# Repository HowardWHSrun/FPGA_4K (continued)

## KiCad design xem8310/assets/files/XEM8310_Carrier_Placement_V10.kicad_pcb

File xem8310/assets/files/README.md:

# HDMI Extension Board V21 downloads

[Full portable KiCad ZIP](HDMI_Extension_Board_V21_Full_KiCad.zip) · [Project guide and checks](../../../hardware/hdmi-extension-board/dated/2026-11-02/v21/project/README.md) · [Schematic PDF](../schematic-v21.pdf)

Extract the entire ZIP to edit. Individual native files are also supplied for inspection. Original saved files are retained in the package records.

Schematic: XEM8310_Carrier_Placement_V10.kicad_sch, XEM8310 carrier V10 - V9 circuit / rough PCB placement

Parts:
C4: 100 nF / 10 V; C4; Manufacturer_PN C0402C104K8PACTU
C5: 220 µF / 25 V; C5; Manufacturer_PN EEE-FK1E221P
C6: 100 nF / 25 V; C6; Manufacturer_PN TMK105BJ104KV-F
C7: 0.1 u; C7; Manufacturer_PN C0402C104K8PACTU
C8: 0.1 u; C8; Manufacturer_PN C0402C104K8PACTU
C9: 0.1 u; C9; Manufacturer_PN C0402C104K8PACTU
C10: 0.1 u; C10; Manufacturer_PN C0402C104K8PACTU
C11: 0.1 u; C11; Manufacturer_PN C0402C104K8PACTU
C12: 0.1 u; C12; Manufacturer_PN C0402C104K8PACTU
C13: 0.1 u; C13; Manufacturer_PN C0402C104K8PACTU
C14: 0.1 u; C14; Manufacturer_PN C0402C104K8PACTU
C15: 0.1 u; C15; Manufacturer_PN C0402C104K8PACTU
C16: 0.1 u; C16; Manufacturer_PN C0402C104K8PACTU
C17: 0.1 u; C17; Manufacturer_PN C0402C104K8PACTU
C18: 0.1 u; C18; Manufacturer_PN C0402C104K8PACTU
C19: 0.1 u; C19; Manufacturer_PN C0402C104K8PACTU
C20: 0.1 u; C20; Manufacturer_PN C0402C104K8PACTU
C27: 0.1 u; C27; Manufacturer_PN C0402C104K8PACTU
C28: 0.1 u; C28; Manufacturer_PN C0402C104K8PACTU
C31: 0.1 u; C31; Manufacturer_PN C0402C104K8PACTU
C32: 0.1 u; C32; Manufacturer_PN C0402C104K8PACTU
C500: 4.7u; C500; Voltage 10V; MPN CL05A475MP5NRNC
C501: 100n; C501; Voltage 10V; MPN C0402C104K8PACTU
C502: 100n; C502; MPN C0402C104K8PACTU
C503: 18p; C503; MPN C0402C180J5GACTU
C504: 18p; C504; MPN C0402C180J5GACTU
C505: 100n; C505; MPN C0402C104K8PACTU
C506: 10n; C506; Voltage 16V; Tolerance 10%; MPN C0402C103K4RACTU
C507: 4.7u; C507; Voltage 6.3V; Tolerance 20%; MPN JMK105BBJ475MV-F
C508: 100n; C508; Voltage 10V; Tolerance 10%; MPN C0402C104K8PACTU
C509: 100n; C509; Voltage 10V; Tolerance 10%; MPN C0402C104K8PACTU
C510: 100n; C510; Voltage 10V; Tolerance 10%; MPN C0402C104K8PACTU
C511: 100n; C511; Voltage 10V; Tolerance 10%; MPN C0402C104K8PACTU
C512: 4.7u; C512; Voltage 6.3V; Tolerance 20%; MPN JMK105BBJ475MV-F
C513: 4.7u; C513; Voltage 6.3V; Tolerance 20%; MPN JMK105BBJ475MV-F
C514: 100n; C514; Voltage 10V; Tolerance 10%; MPN C0402C104K8PACTU
C515: 4.7u; C515; Voltage 6.3V; Tolerance 20%; MPN JMK105BBJ475MV-F
C516: 100n; C516; Voltage 10V; Tolerance 10%; MPN C0402C104K8PACTU
C517: 100n; C517; Voltage 10V; Tolerance 10%; MPN C0402C104K8PACTU
C518: 100n; C518; Voltage 10V; Tolerance 10%; MPN C0402C104K8PACTU
C519: 10n; C519; Voltage 16V; Tolerance 10%; MPN C0402C103K4RACTU
C520: 2.2uF 10V X7R; C520
C521: 2.2uF 10V X7R; C521
C600, C601: 2.2uF / 10V; C_0603_1608Metric; MPN GRM188R71A225KE15D
C610, C611, C612, C613, C620, C621, C622, C623, C710, C721, C722, C723, C724, C725, C726, C727, C728: 100nF / 16V; C_0603_1608Metric; MPN GRM188R71C104KA01D
C700: 100nF / 10V X7R; C700
C800, C801: 10uF / 25V X7R; C_1206_3216Metric; MPN GRM31CR71E106KA12L
C802, C803: 100nF / 25V X7R; C_0603_1608Metric; MPN GRM188R71E104KA01D
C810, C811, C812: 22uF / 16V X7R; C_1210_3225Metric; MPN GRM32ER71C226KEA8L
C1101, C1102, C1201, C1202, C1301, C1302, C1401, C1402, C1501, C1502, C1601, C1602, C1701, C1702, C1801, C1802: 100nF / 25V; C_AC_100nF_0603; Manufacturer_PN GRM188R71E104KA01D
C8100, C8101, C8200, C8201, C8300, C8301, C8400, C8401, C8500, C8501, C8600, C8601, C8700, C8701, C8800, C8801: 1uF / 25V X7R; C_0603_1608Metric; MPN GRM188R71E105KA12D
C8102, C8202, C8302, C8402, C8502, C8602, C8702, C8802: 47nF / 25V X7R; C_0603_1608Metric; MPN GRM188R71E473KA01D
D1: Green; D1; Manufacturer_PN 598-8070-107F
D2: Green; D2; Manufacturer_PN 598-8070-107F
D500: USBLC6-2SC6; D500
D810, D811, D812, D813, D814, D815, D816, D817: BAT54WS; D_SOD-323; MPN BAT54WS-7-F
FB500: 600R; FB500; MPN MI0603J601R-10
FB501: 600R; FB501; MPN MI0603J601R-10
FB502: 600R; FB502; MPN MI0603J601R-10
FB503: 220R @100MHz; FB503; MANUFACTURER_PN BLM21PG221SN1D
J3: 87831-1420; J3; Manufacturer_PN 87831-1420
J4: PJ-102AH; J4; Manufacturer_PN PJ-102AH
J5: 0455580003; J5; Manufacturer_PN 0455580003
J6: PCIe x4 electrical / x8 BRK edge; J6
J101, J102, J103, J104, J105, J106, J107, J108: 467651001 / GT + GPIO; MicroHDMI_467651001
J500: USB4110-GF-A; J500; MANUFACTURER_PN USB4110-GF-A
L800: 2.2uH / 20%; L_Coilcraft_XAL7070-XXX; MPN XAL7070-222MEC
MC1: BTE-040-01-F-D-A; MC1
MC2: BTE-040-01-F-D-A; MC2
MC3: QTH-040-01-F-D-DP-A; MC3
Q1: SI1922EDH-T1-GE3; Q1; Manufacturer_PN SI1922EDH-T1-GE3
R1: 0; R1; Manufacturer_PN CRCW06030000Z0EA; not fitted
R2: 0; R2; Manufacturer_PN CRCW06030000Z0EA
R3: 549 Ω / 1%; R3; Manufacturer_PN CRCW0402549RFKED
R4: 2.00 kΩ / 1%; R4; Manufacturer_PN CRCW04022K00FKED
R6: 0R / internal ADC ref; R6
R7: 0; R7; Manufacturer_PN CRCW06030000Z0EA
R8: 0; R8; Manufacturer_PN CRCW06030000Z0EA; not fitted
R9: 0; R9; Manufacturer_PN CRCW06030000Z0EA
R10: 0; R10; Manufacturer_PN CRCW06030000Z0EA
R11: 0; R11; Manufacturer_PN CRCW06030000Z0EA
R12: NoLoad; R12; not fitted
R13: 200 k; R13; Manufacturer_PN CRCW0402200KFKED
R14: 4.75 k; R14; Manufacturer_PN CRCW04024K75FKED
R15: 4.75 k; R15; Manufacturer_PN CRCW04024K75FKED
R16: NoLoad; R16; not fitted
R17: NoLoad; R17; not fitted
R18: 100 k; R18; Manufacturer_PN CRCW0402100KFKED
R20: NoLoad; R20; not fitted
R21: NoLoad; R21; not fitted
R22: NoLoad; R22; not fitted
R23: 200 k; R23; Manufacturer_PN CRCW0402200KFKED
R24: 100 k; R24; Manufacturer_PN CRCW0402100KFKED
R25: 100 k; R25; Manufacturer_PN CRCW0402100KFKED
R26: NoLoad; R26; not fitted
R27: 0; R27; Manufacturer_PN CRCW04020000Z0ED; not fitted
R28: 0; R28; Manufacturer_PN CRCW04020000Z0ED; not fitted
R29: 0; R29; Manufacturer_PN CRCW04020000Z0ED
R30: 4.75 k; R30; Manufacturer_PN CRCW04024K75FKED
R31: 4.75 k; R31; Manufacturer_PN CRCW04024K75FKED
R32: 100 k; R32; Manufacturer_PN CRCW0402100KFKED
R33: 100 k; R33; Manufacturer_PN CRCW0402100KFKED
R500: 5.1k 1%; R500; MPN CRCW04025K10FKEDC
R501: 5.1k 1%; R501; MPN CRCW04025K10FKEDC
R502: 100k; R502; Tolerance 1%; MPN CRCW0402100KFKED
R503: 100k; R503; Tolerance 1%; MPN CRCW0402100KFKED
R504: 2k; R504; Tolerance 1%; MPN CRCW04022K00FKED
R505: 10k; R505; Tolerance 1%; MPN CRCW040210K0FKED
R506: 10k; R506; Tolerance 1%; MPN CRCW040210K0FKED
R507: 12k 1%; R507; Tolerance 1%; MPN CRCW040212K0FKED
R508: 10k; R508
R509: 10k; R509
R600, R610, R611, R620, R621, R631, R641, R651, R661, R671, R681, R691, R720, R721, R722, R723, R724, R725, R726, R727, R8104, R8204, R8304, R8404, R8504, R8604, R8704, R8804: 10k / 1%; R_0603_1608Metric; MPN RC0603FR-0710KL
R612: 1M / 1%; R_0603_1608Metric; MPN RC0603FR-071ML
R613, R623, R804: 100k / 1%; R_0603_1608Metric; MPN RC0603FR-07100KL
R614, R615, R616, R624, R625, R626: 33R / 1%; R_0603_1608Metric; MPN RC0603FR-0733RL
R622: 68k / 1%; R_0603_1608Metric; MPN RC0603FR-0768KL
R700: 10k; R700
R701: 100k; R701
R730, R731, R732, R733, R734, R735, R736, R737: 1k / 1%; R_0603_1608Metric; MPN RC0603FR-071KL
R738: 140k / 0.1%; R_0603_1608Metric; MPN RT0603BRD07140KL
R739: 49.9k / 0.1%; R_0603_1608Metric; MPN RT0603BRD0749K9L
R800: 169k / 1%; R_0603_1608Metric; MPN RC0603FR-07169KL
R801: 36.1k / 1%; R_0603_1608Metric; MPN RT0603FRE0736K1L
R802: 45.3k / 0.1%; R_0603_1608Metric; MPN RT0603BRD0745K3L
R803, R8101, R8103, R8201, R8203, R8301, R8303, R8401, R8403, R8501, R8503, R8601, R8603, R8701, R8703, R8801, R8803: 10.0k / 0.1%; R_0603_1608Metric; MPN RT0603BRD0710KL
R8100, R8200, R8300, R8400, R8500, R8600, R8700, R8800: 15.0k / 0.1%; R_0603_1608Metric; MPN RT0603BRD0715KL
R8102, R8202, R8302, R8402, R8502, R8602, R8702, R8802: 19.1k / 0.1%; R_0603_1608Metric; MPN RT0603BRD0719K1L
R8105, R8205, R8305, R8405, R8505, R8605, R8705, R8805: 100R / 1%; R_0603_1608Metric; MPN RC0603FR-07100RL
R8106, R8206, R8306, R8406, R8506, R8606, R8706, R8806: 5.00k / 0.1%; R_0805_2012Metric; MPN PNM0805E5001BST5
SW600: Grayhill56P30_1P12T_N; Grayhill_56P30_1P12T_N; MPN 56P30-01-1-12N-F
SW700: JS202011JCQN; SW700
SW810, SW811, SW812, SW813, SW814, SW815, SW816, SW817: PRESS: OFF / RESET; SW_SPST_TL3342; MPN TL3342F160QG
TP9: SMDAT_VIO; TP9
TP10: SMDAT_PCIE; TP10
TP11: SMCLK_PCIE; TP11
TP12: SMCLK_VIO; TP12
TP13: PERST_VIO; TP13
TP14: PERST_PCIE; TP14
TP15: WAKE_VIO; TP15
TP16: WAKE_PCIE; TP16
TP20: +12V_PCIE_C; TP20
TP21: FAULT; TP21
TP800: BUCK_PG; TestPoint_Pad_D1.0mm
TP801: HDMI_3V3_RAW; TestPoint_Pad_D1.0mm
TP810, TP811, TP812, TP813, TP814, TP815, TP816, TP817: PORT_FAULT_N; TestPoint_Pad_D1.0mm
U2: PCA9306DCUR; U2; Manufacturer_PN PCA9306DCUR
U4: SN74AXC1T45DCK; U4; Manufacturer_PN SN74AXC1T45DCK
U5: AP22653AW6-7; U5; Manufacturer_PN AP22653AW6-7
U6: PCA9306DCUR; U6; Manufacturer_PN PCA9306DCUR
U501: FT232HQ; U501; MANUFACTURER_PN FT232HQ
U505: 93LC56B-E/MS; U505; MANUFACTURER_PN 93LC56B-E/MS
U506: TLV75533PDBVR; U506
U600: TLV75518PDBVR; SOT-23-5; MPN TLV75518PDBVR
U610, U611: TXU0304PWR; TSSOP-14_4.4x5mm_P0.65mm; MPN TXU0304PWR
U620: TPS3808G18DBVR; SOT-23-6; MPN TPS3808G18DBVR
U621: TPS3808G01DBVR; SOT-23-6; MPN TPS3808G01DBVR
U630, U631: SN74LVC1G17DBVR; SOT-23-5; MPN SN74LVC1G17DBVR
U700: TMUX1574PWR; U700
U710: SN74LVC540APWR; TSSOP-20_4.4x6.5mm_P0.65mm; MPN SN74LVC540APWR
U721, U722, U723, U724, U725, U726, U727, U728: TS3A27518EPWR; TSSOP-24_4.4x7.8mm_P0.65mm; MPN TS3A27518EPWR
U800: TPS56637RPAR; TI_RPA0010A_HotRod_3x3mm; MPN TPS56637RPAR
U810, U811, U812, U813, U814, U815, U816, U817: TPS259470LRPWR; TI_RPW0010A_HotRod_2x2mm; MPN TPS259470LRPWR
Y500: 12MHz; Y500; MPN ABM8-12.000MHZ-B2-T

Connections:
+1.2V_DDR: MC3.80 (+1.2V_DDR), R2.2
+1.8V: C4.1, C700.1, J3.2 (VREF), MC1.2 (+1.8V), R612.1, SW700.7 (EXTERNAL), U620.5 (SENSE_1V67), U700.16 (VDD)
+3.3V: MC2.70 (+3.3V), R3.2, R30.2, R31.2
+3.3VAUX_PCIE: C31.2, R13.2, R16.2, R17.2, R23.2, R26.2, U5.6 (OUT)
+3.3VAUX_PCIE_C: C32.2, J6.B10 (3.3Vaux), R18.2, U5.1 (IN)
+3.3V_PCIE_C: C12.2, J6.A9 (+3.3V), J6.A10 (+3.3V), J6.B8 (+3.3V), R21.2, U4.6 (Vccb)
+12V_PCIE_C: J6.A2 (+12V), J6.A3 (+12V), J6.B1 (+12V), J6.B2 (+12V), J6.B3 (+12V), TP20.1 (PIN_1)
+VDCIN: C5.1 (+), C6.2, C800.1, C801.1, C802.1, J4.1 (+VDCIN), J5.1, J5.2, J5.3, MC2.1 (+VDCIN), MC2.2 (+VDCIN), MC2.3 (+VDCIN), MC2.4 (+VDCIN), R4.2, R800.1, U800.8 (VIN)
/B64_L1N: J101.14 (GPIO_STIM_N), MC1.12 (B64_L1N)
/B64_L1P: J101.12 (GPIO_STIM_P), MC1.10 (B64_L1P)
/B64_L2N: J102.14 (GPIO_STIM_N), MC1.16 (B64_L2N)
/B64_L2P: J102.12 (GPIO_STIM_P), MC1.14 (B64_L2P)
/B64_L3N: J103.14 (GPIO_STIM_N), MC1.15 (B64_L3N)
/B64_L3P: J103.12 (GPIO_STIM_P), MC1.13 (B64_L3P)
/B64_L4N: J104.14 (GPIO_STIM_N), MC1.8 (B64_L4N)
/B64_L4P: J104.12 (GPIO_STIM_P), MC1.6 (B64_L4P)
/B64_L5N: J105.14 (GPIO_STIM_N), MC1.7 (B64_L5N)
/B64_L5P: J105.12 (GPIO_STIM_P), MC1.5 (B64_L5P)
/B64_L6N: J106.14 (GPIO_STIM_N), MC1.11 (B64_L6N)
/B64_L6P: J106.12 (GPIO_STIM_P), MC1.9 (B64_L6P)
/B64_L7N: J107.14 (GPIO_STIM_N), MC1.23 (B64_L7N)
/B64_L7P: J107.12 (GPIO_STIM_P), MC1.21 (B64_L7P)
/B64_L8N: J108.14 (GPIO_STIM_N), MC1.20 (B64_L8N)
/B64_L8P: J108.12 (GPIO_STIM_P), MC1.18 (B64_L8P)
/FTDI1V8_ANALOG: C518.2, U501.37 (VCCA)
/FTDI1V8_CORE: C517.2, U501.38 (VCORE)
/FTDI3V3_PHY: C515.1, C516.1, FB501.2, U501.3 (VPHY)
/FTDI3V3_PLL: C513.1, C514.1, FB500.2, U501.8 (VPLL)
/FTDI5V_FILTERED: C500.1, C501.1, FB502.2, U501.40 (VREGIN)
/FTDI_EECLK: R503.2, U501.44 (EECLK), U505.2 (CLK)
/FTDI_EECS: R502.1, U501.45 (EECS), U505.1 (CS)
/FTDI_EEDATA: R504.1, U501.43 (EEDATA), U505.3 (DI)
/HDMI_3V3_PG: D810.1 (K), D811.1 (K), D812.1 (K), D813.1 (K), D814.1 (K), D815.1 (K), D816.1 (K), D817.1 (K), R804.1, TP800.1 (1_1), U800.4 (PG)
/HDMI_3V3_RAW: C810.1, C811.1, C812.1, C8100.1, C8200.1, C8300.1, C8400.1, C8500.1, C8600.1, C8700.1, C8800.1, L800.2, R802.1, R804.2, R8100.1, R8102.1, R8104.1, R8200.1, R8202.1, R8204.1, R8300.1, R8302.1, R8304.1, R8400.1, R8402.1, R8404.1, R8500.1, R8502.1, R8504.1, R8600.1, R8602.1, R8604.1, R8700.1, R8702.1, R8704.1, R8800.1, R8802.1, R8804.1, TP801.1 (1_1), U810.5 (IN), U811.5 (IN), U812.5 (IN), U813.5 (IN), U814.5 (IN), U815.5 (IN), U816.5 (IN), U817.5 (IN)
/MGT_RXN0_224: C1102.2, MC3.3 (MGT_RXN0_224)
/MGT_RXN0_226: C1502.2, MC3.43 (MGT_RXN0_226)
/MGT_RXN1_224: C1202.2, MC3.7 (MGT_RXN1_224)
/MGT_RXN1_226: C1602.2, MC3.47 (MGT_RXN1_226)
/MGT_RXN2_224: C1302.2, MC3.11 (MGT_RXN2_224)
/MGT_RXN2_226: C1702.2, MC3.51 (MGT_RXN2_226)
/MGT_RXN3_224: C1402.2, MC3.15 (MGT_RXN3_224)
/MGT_RXN3_226: C1802.2, MC3.55 (MGT_RXN3_226)
/MGT_RXP0_224: C1101.2, MC3.1 (MGT_RXP0_224)
/MGT_RXP0_226: C1501.2, MC3.41 (MGT_RXP0_226)
/MGT_RXP1_224: C1201.2, MC3.5 (MGT_RXP1_224)
/MGT_RXP1_226: C1601.2, MC3.45 (MGT_RXP1_226)
/MGT_RXP2_224: C1301.2, MC3.9 (MGT_RXP2_224)
/MGT_RXP2_226: C1701.2, MC3.49 (MGT_RXP2_226)
/MGT_RXP3_224: C1401.2, MC3.13 (MGT_RXP3_224)
/MGT_RXP3_226: C1801.2, MC3.53 (MGT_RXP3_226)
/P1_3V3_PROTECTED: C8101.1, J101.19 (3V3_PROTECTED), U810.6 (OUT)
/P1_POWER_FAULT_N: R8104.2, TP810.1 (1_1), U810.4 (nFLT)
/P2_3V3_PROTECTED: C8201.1, J102.19 (3V3_PROTECTED), U811.6 (OUT)
/P2_POWER_FAULT_N: R8204.2, TP811.1 (1_1), U811.4 (nFLT)
/P3_3V3_PROTECTED: C8301.1, J103.19 (3V3_PROTECTED), U812.6 (OUT)
/P3_POWER_FAULT_N: R8304.2, TP812.1 (1_1), U812.4 (nFLT)
/P4_3V3_PROTECTED: C8401.1, J104.19 (3V3_PROTECTED), U813.6 (OUT)
/P4_POWER_FAULT_N: R8404.2, TP813.1 (1_1), U813.4 (nFLT)
/P5_3V3_PROTECTED: C8501.1, J105.19 (3V3_PROTECTED), U814.6 (OUT)
/P5_POWER_FAULT_N: R8504.2, TP814.1 (1_1), U814.4 (nFLT)
/P6_3V3_PROTECTED: C8601.1, J106.19 (3V3_PROTECTED), U815.6 (OUT)
/P6_POWER_FAULT_N: R8604.2, TP815.1 (1_1), U815.4 (nFLT)
/P7_3V3_PROTECTED: C8701.1, J107.19 (3V3_PROTECTED), U816.6 (OUT)
/P7_POWER_FAULT_N: R8704.2, TP816.1 (1_1), U816.4 (nFLT)
/P8_3V3_PROTECTED: C8801.1, J108.19 (3V3_PROTECTED), U817.6 (OUT)
/P8_POWER_FAULT_N: R8804.2, TP817.1 (1_1), U817.4 (nFLT)
/XEM_JTAG_MASTER_SEL: R701.1, SW700.6 (MUX_SEL_COMMON), U700.1 (SEL)
B64_L17N: MC1.44 (B64_L17N), R11.2
B64_L17P: MC1.42 (B64_L17P), R10.2
B64_L20N: MC1.40 (B64_L20N), R9.2
B64_L20P: MC1.38 (B64_L20P), R8.2
B67_T3U_N12: MC3.78 (B67_T3U_N12), R7.2
DGND: C4.2, C5.2 (-), C6.1, C9.1, C10.1, C11.1, C12.1, C27.1, C28.1, C31.1, C32.1, C520.2, C521.2, C600.2, C601.2, C610.2, C611.2, C612.2, C613.2, C620.2, C621.2, C622.2, C623.2, C700.2, C710.2, C721.2, C722.2, C723.2, C724.2, C725.2, C726.2, C727.2, C728.2, C800.2, C801.2, C802.2, C810.2, C811.2, C812.2, C8100.2, C8101.2, C8102.2, C8200.2, C8201.2, C8202.2, C8300.2, C8301.2, C8302.2, C8400.2, C8401.2, C8402.2, C8500.2, C8501.2, C8502.2, C8600.2, C8601.2, C8602.2, C8700.2, C8701.2, C8702.2, C8800.2, C8801.2, C8802.2, D1.1 (K), D2.1 (K), D500.2 (GND), J3.1 (DGND), J3.3 (DGND), J3.5 (DGND), J3.7 (DGND), J3.9 (DGND), J3.11 (DGND), J3.13 (DGND), J4.2 (DGND), J5.4, J5.5, J5.6, J6.A4 (GND), J6.A12 (GND), J6.A15 (GND), J6.A18 (GND), J6.A20 (GND), J6.A23 (GND), J6.A24 (GND), J6.A27 (GND), J6.A28 (GND), J6.A31 (GND), J6.A34 (GND), J6.A37 (GND), J6.A38 (GND), J6.A41 (GND), J6.A42 (GND), J6.A45 (GND), J6.A46 (GND), J6.A49 (GND), J6.B4 (GND), J6.B7 (GND), J6.B13 (GND), J6.B16 (GND), J6.B18 (GND), J6.B21 (GND), J6.B22 (GND), J6.B25 (GND), J6.B26 (GND), J6.B29 (GND), J6.B32 (GND), J6.B35 (GND), J6.B36 (GND), J6.B39 (GND), J6.B40 (GND), J6.B43 (GND), J6.B44 (GND), J6.B47 (GND), J6.B49 (GND), J101.4 (GND), J101.7 (GND), J101.10 (GND), J101.13 (GND), J101.16 (GND), J101.SH (SHELL), J102.4 (GND), J102.7 (GND), J102.10 (GND), J102.13 (GND), J102.16 (GND), J102.SH (SHELL), J103.4 (GND), J103.7 (GND), J103.10 (GND), J103.13 (GND), J103.16 (GND), J103.SH (SHELL), J104.4 (GND), J104.7 (GND), J104.10 (GND), J104.13 (GND), J104.16 (GND), J104.SH (SHELL), J105.4 (GND), J105.7 (GND), J105.10 (GND), J105.13 (GND), J105.16 (GND), J105.SH (SHELL), J106.4 (GND), J106.7 (GND), J106.10 (GND), J106.13 (GND), J106.16 (GND), J106.SH (SHELL), J107.4 (GND), J107.7 (GND), J107.10 (GND), J107.13 (GND), J107.16 (GND), J107.SH (SHELL), J108.4 (GND), J108.7 (GND), J108.10 (GND), J108.13 (GND), J108.16 (GND), J108.SH (SHELL), MC1.3 (DGND), MC1.29 (DGND), MC1.30 (DGND), MC1.59 (DGND), MC1.60 (DGND), MC1.77 (DGND), MC1.78 (DGND), MC2.5 (DGND), MC2.6 (DGND), MC2.7 (DGND), MC2.8 (DGND), MC2.33 (DGND), MC2.34 (DGND), MC2.67 (DGND), MC2.68 (DGND), MC2.73 (DGND), MC3.0 (CENTER_GROUND), Q1.1 (S1), Q1.4 (S2), R12.1, R22.1, R24.1, R32.1, R33.1, R600.2, R611.2, R612.2, R613.2, R621.1, R622.2, R623.2, R631.1, R641.1, R651.1, R661.1, R671.1, R681.1, R691.1, R700.2, R701.2, R730.2, R731.2, R732.2, R733.2, R734.2, R735.2, R736.2, R737.2, R739.1, R801.2, R803.2, R8101.2, R8103.2, R8106.2, R8201.2, R8203.2, R8206.2, R8301.2, R8303.2, R8306.2, R8401.2, R8403.2, R8406.2, R8501.2, R8503.2, R8506.2, R8601.2, R8603.2, R8606.2, R8701.2, R8703.2, R8706.2, R8801.2, R8803.2, R8806.2, SW700.3 (EXTERNAL), SW700.5 (ONBOARD), SW810.2, SW811.2, SW812.2, SW813.2, SW814.2, SW815.2, SW816.2, SW817.2, U2.1 (GND), U4.2 (GND), U4.5 (DIR), U5.2 (GND), U6.1 (GND), U506.2 (GND), U600.2 (GND), U610.7 (GND), U611.7 (GND), U620.2 (GND), U621.2 (GND), U630.3 (GND), U631.3 (GND), U700.8 (GND), U700.15 (~EN), U710.1 (~OE1), U710.10 (GND), U710.19 (~OE2), U721.5 (GND), U722.5 (GND), U723.5 (GND), U724.5 (GND), U725.5 (GND), U726.5 (GND), U727.5 (GND), U728.5 (GND), U800.3 (AGND), U800.9 (PGND), U800.10 (MODE), U810.8 (GND), U811.8 (GND), U812.8 (GND), U813.8 (GND), U814.8 (GND), U815.8 (GND), U816.8 (GND), U817.8 (GND); also elsewhere on the board
EXT_JTAG_TCK: J3.6 (TCK), U700.3 (S1B)
EXT_JTAG_TDI: J3.10 (TDI), U700.10 (S3B)
EXT_JTAG_TDO: J3.8 (TDO), U700.13 (S4B)
EXT_JTAG_TMS: J3.4 (TMS), U700.6 (S2B)
FTDI3V3: C505.1, C507.1, C508.1, C509.1, C510.1, C511.1, C512.1, FB500.1, FB501.1, R503.1, R505.2, R506.1, R508.2, R509.2, U501.12 (VCCIO), U501.24 (VCCIO), U501.39 (VCCD), U501.46 (VCCIO), U505.8 (VCC)
GND: C500.2, C501.2, C502.2, C503.2, C504.2, C505.2, C506.1, C507.2, C508.2, C509.2, C510.2, C511.2, C512.2, C513.2, C514.2, C515.2, C516.2, C517.1, C518.1, C519.2, FB503.1, J500.A1 (GND), J500.A12 (GND), J500.B1 (GND), J500.B12 (GND), R500.1, R501.2, R502.2, R507.2, U501.4 (AGND), U501.9 (AGND), U501.10 (GND), U501.11 (GND), U501.22 (GND), U501.23 (GND), U501.35 (GND), U501.36 (GND), U501.41 (AGND), U501.42 (TEST), U501.47 (GND), U501.48 (GND), U501.PAD, U505.5 (VSS), Y500.2 (CASE), Y500.4 (CASE)
GNDADC: MC2.77 (GNDADC), R6.1
HOST_TCK: U501.13 (ADBUS0_/_TCK_/_SK), U610.2 (A1_TCK), U611.2 (A1_TCK)
HOST_TDI: U501.14 (ADBUS1_/_TDI_/_DO), U610.3 (A2_TDI), U611.3 (A2_TDI)
HOST_TDO: R509.1, U501.15 (ADBUS2_/_TDO_/_DI), U610.5 (A4Y_TDO), U611.5 (A4Y_TDO)
HOST_TMS: U501.16 (ADBUS3_/_TMS_/_CS), U610.4 (A3_TMS), U611.4 (A3_TMS)
HS_MUX_DISABLE_1: R720.2, U710.18 (Y1_INVERT), U721.20 (DISABLE_HIGH)
HS_MUX_DISABLE_2: R721.2, U710.17 (Y2_INVERT), U722.20 (DISABLE_HIGH)
HS_MUX_DISABLE_3: R722.2, U710.16 (Y3_INVERT), U723.20 (DISABLE_HIGH)
HS_MUX_DISABLE_4: R723.2, U710.15 (Y4_INVERT), U724.20 (DISABLE_HIGH)
HS_MUX_DISABLE_5: R724.2, U710.14 (Y5_INVERT), U725.20 (DISABLE_HIGH)
HS_MUX_DISABLE_6: R725.2, U710.13 (Y6_INVERT), U726.20 (DISABLE_HIGH)
HS_MUX_DISABLE_7: R726.2, U710.12 (Y7_INVERT), U727.20 (DISABLE_HIGH)
HS_MUX_DISABLE_8: R727.2, U710.11 (Y8_INVERT), U728.20 (DISABLE_HIGH)
HS_SENSE_DIV: R738.2, R739.2, U621.5 (SENSE_0V405)
HS_TARGET_SENSE: R622.1, R738.1, U721.10 (COM5), U722.10 (COM5), U723.10 (COM5), U724.10 (COM5), U725.10 (COM5), U726.10 (COM5), U727.10 (COM5), U728.10 (COM5)
HS_TCK_1V8: R624.2, U721.4 (COM1), U722.4 (COM1), U723.4 (COM1), U724.4 (COM1), U725.4 (COM1), U726.4 (COM1), U727.4 (COM1), U728.4 (COM1)
HS_TDI_1V8: R625.2, U721.6 (COM2), U722.6 (COM2), U723.6 (COM2), U724.6 (COM2), U725.6 (COM2), U726.6 (COM2), U727.6 (COM2), U728.6 (COM2)
HS_TDO_1V8: U611.10 (B4_TDO), U721.9 (COM4), U722.9 (COM4), U723.9 (COM4), U724.9 (COM4), U725.9 (COM4), U726.9 (COM4), U727.9 (COM4), U728.9 (COM4)
HS_TMS_1V8: R626.2, U721.7 (COM3), U722.7 (COM3), U723.7 (COM3), U724.7 (COM3), U725.7 (COM3), U726.7 (COM3), U727.7 (COM3), U728.7 (COM3)
HS_USB_OE: R623.1, U611.8 (OE), U631.4 (Y)
JTAG_LOCAL_1V8: C601.1, C613.1, C623.1, U600.5 (OUT_1V8), U610.14 (VCCB_1V8), U611.14 (VCCB_1V8)
JTAG_LOGIC_3V3: C521.1, C600.1, C610.1, C611.1, C612.1, C620.1, C621.1, C622.1, C710.1, C721.1, C722.1, C723.1, C724.1, C725.1, C726.1, C727.1, C728.1, R610.1, R620.1, R720.1, R721.1, R722.1, R723.1, R724.1, R725.1, R726.1, R727.1, SW700.1 (ONBOARD), U506.5 (OUT), U600.1 (IN), U600.3 (EN), U610.1 (VCCA_3V3), U611.1 (VCCA_3V3), U620.6 (VDD), U621.6 (VDD), U630.5 (VCC), U631.5 (VCC), U710.20 (VCC_3V3), U721.8 (VCC_3V3), U721.14 (IN2_HIGH), U721.24 (IN1_HIGH), U722.8 (VCC_3V3), U722.14 (IN2_HIGH), U722.24 (IN1_HIGH), U723.8 (VCC_3V3), U723.14 (IN2_HIGH), U723.24 (IN1_HIGH), U724.8 (VCC_3V3), U724.14 (IN2_HIGH), U724.24 (IN1_HIGH), U725.8 (VCC_3V3), U725.14 (IN2_HIGH), U725.24 (IN1_HIGH), U726.8 (VCC_3V3), U726.14 (IN2_HIGH), U726.24 (IN1_HIGH), U727.8 (VCC_3V3), U727.14 (IN2_HIGH), U727.24 (IN1_HIGH), U728.8 (VCC_3V3), U728.14 (IN2_HIGH), U728.24 (IN1_HIGH)
JTAG_TCK: MC2.76 (JTAG_TCK), U700.4 (D1)
JTAG_TDI: MC2.74 (JTAG_TDI), U700.9 (D3)
JTAG_TDO: MC2.71 (JTAG_TDO), U700.12 (D4)
JTAG_TMS: MC2.72 (JTAG_TMS), U700.7 (D2)
MGT_REFCLK1N_225_C: C8.2, MC3.19 (MGT_REFCLK1N_225_C)
MGT_REFCLK1P_225_C: C7.2, MC3.17 (MGT_REFCLK1P_225_C)
MGT_RXN0_225: J6.B28 (PETn3), MC3.23 (MGT_RXN0_225)
MGT_RXN1_225: J6.B24 (PETn2), MC3.27 (MGT_RXN1_225)
MGT_RXN2_225: J6.B20 (PETn1), MC3.31 (MGT_RXN2_225)
MGT_RXN3_225: J6.B15 (PETn0), MC3.35 (MGT_RXN3_225)
MGT_RXP0_225: J6.B27 (PETp3), MC3.21 (MGT_RXP0_225)
MGT_RXP1_225: J6.B23 (PETp2), MC3.25 (MGT_RXP1_225)
MGT_RXP2_225: J6.B19 (PETp1), MC3.29 (MGT_RXP2_225)
MGT_RXP3_225: J6.B14 (PETp0), MC3.33 (MGT_RXP3_225)
MGT_TXN0_225: C20.2, MC3.24 (MGT_TXN0_225)
MGT_TXN1_225: C18.2, MC3.28 (MGT_TXN1_225)
MGT_TXN2_225: C16.2, MC3.32 (MGT_TXN2_225)
MGT_TXN3_225: C14.2, MC3.36 (MGT_TXN3_225)
MGT_TXP0_225: C19.2, MC3.22 (MGT_TXP0_225)
MGT_TXP1_225: C17.2, MC3.26 (MGT_TXP1_225)
MGT_TXP2_225: C15.2, MC3.30 (MGT_TXP2_225)
MGT_TXP3_225: C13.2, MC3.34 (MGT_TXP3_225)
unnamed: C502.1, FB503.2, J500.M1 (SHELL), J500.M2 (SHELL), J500.M3 (SHELL), J500.M4 (SHELL)
unnamed: C8102.1, R8105.2
unnamed: C8202.1, R8205.2
unnamed: C8302.1, R8305.2
unnamed: C8402.1, R8405.2
unnamed: C8502.1, R8505.2
unnamed: C8602.1, R8605.2
unnamed: C8702.1, R8705.2
unnamed: C8802.1, R8805.2
unnamed: D1.2 (A), R3.1
unnamed: D2.2 (A), R4.1
unnamed: D810.2 (A), R8100.2, R8101.1, SW810.1, U810.1 (EN_UVLO)
unnamed: D811.2 (A), R8200.2, R8201.1, SW811.1, U811.1 (EN_UVLO)
unnamed: D812.2 (A), R8300.2, R8301.1, SW812.1, U812.1 (EN_UVLO)
unnamed: D813.2 (A), R8400.2, R8401.1, SW813.1, U813.1 (EN_UVLO)
unnamed: D814.2 (A), R8500.2, R8501.1, SW814.1, U814.1 (EN_UVLO)
unnamed: D815.2 (A), R8600.2, R8601.1, SW815.1, U815.1 (EN_UVLO)
unnamed: D816.2 (A), R8700.2, R8701.1, SW816.1, U816.1 (EN_UVLO)
unnamed: D817.2 (A), R8800.2, R8801.1, SW817.1, U817.1 (EN_UVLO)
unnamed: C1102.1, J101.5 (GT_REC_N)
unnamed: C1101.1, J101.3 (GT_REC_P)
unnamed: C1202.1, J102.5 (GT_REC_N)
unnamed: C1201.1, J102.3 (GT_REC_P)
unnamed: C1302.1, J103.5 (GT_REC_N)
unnamed: C1301.1, J103.3 (GT_REC_P)
unnamed: C1402.1, J104.5 (GT_REC_N)
unnamed: C1401.1, J104.3 (GT_REC_P)
unnamed: C1502.1, J105.5 (GT_REC_N)
unnamed: C1501.1, J105.3 (GT_REC_P)
unnamed: C1602.1, J106.5 (GT_REC_N)
unnamed: C1601.1, J106.3 (GT_REC_P)
unnamed: C1702.1, J107.5 (GT_REC_N)
unnamed: C1701.1, J107.3 (GT_REC_P)
unnamed: C1802.1, J108.5 (GT_REC_N)
unnamed: C1801.1, J108.3 (GT_REC_P)
unnamed: J500.A5 (CC1), R500.2
unnamed: J500.B5 (CC2), R501.1
unnamed: R508.1, U501.17 (ADBUS4_/_GPIOL0)
unnamed: C503.1, U501.1 (OSCI), Y500.1 (OSC1)
unnamed: C504.1, U501.2 (OSCO), Y500.3 (OSC2)
unnamed: R507.1, U501.5 (REF)
unnamed: C519.1, R506.2, U501.34 (~RESET)
unnamed: R504.2, R505.1, U505.4 (DO)
unnamed: R614.1, U610.13 (B1Y_TCK)
unnamed: R615.1, U610.12 (B2Y_TDI)
unnamed: R616.1, U610.11 (B3Y_TMS)
unnamed: R624.1, U611.13 (B1Y_TCK)
unnamed: R625.1, U611.12 (B2Y_TDI)
unnamed: R626.1, U611.11 (B3Y_TMS)
unnamed: R610.2, U620.1 (~RESET), U630.2 (A)
unnamed: R620.2, U621.1 (~RESET), U631.2 (A)
unnamed: C803.1, U800.7 (BOOT)
unnamed: R800.2, R801.1, U800.1 (EN)
unnamed: R802.2, R803.1, U800.2 (FB)
unnamed: C803.2, L800.1, U800.6 (SW)
unnamed: R8105.1, U810.7 (DVDT)
unnamed: R8106.1, U810.9 (ILM)
unnamed: R8102.2, R8103.1, U810.2 (OVLO)
unnamed: R8205.1, U811.7 (DVDT)
unnamed: R8206.1, U811.9 (ILM)
unnamed: R8202.2, R8203.1, U811.2 (OVLO)
unnamed: R8305.1, U812.7 (DVDT)
unnamed: R8306.1, U812.9 (ILM)
unnamed: R8302.2, R8303.1, U812.2 (OVLO)
unnamed: R8405.1, U813.7 (DVDT)
unnamed: R8406.1, U813.9 (ILM)
unnamed: R8402.2, R8403.1, U813.2 (OVLO)
unnamed: R8505.1, U814.7 (DVDT)
unnamed: R8506.1, U814.9 (ILM)
unnamed: R8502.2, R8503.1, U814.2 (OVLO)
unnamed: R8605.1, U815.7 (DVDT)
unnamed: R8606.1, U815.9 (ILM)
unnamed: R8602.2, R8603.1, U815.2 (OVLO)
unnamed: R8705.1, U816.7 (DVDT)
unnamed: R8706.1, U816.9 (ILM)
unnamed: R8702.2, R8703.1, U816.2 (OVLO)
unnamed: R8805.1, U817.7 (DVDT)
unnamed: R8806.1, U817.9 (ILM)
unnamed: R8802.2, R8803.1, U817.2 (OVLO)
NetJ6_B17: J6.B17 (PRSNT2#), R27.1
NetJ6_B31: J6.B31 (PRSNT2#), R28.1
NetJ6_B48: J6.B48 (PRSNT2#), R29.1
P1_TARGET_SENSE: J101.1 (TARGET_SENSE_1V8), U721.18 (NO5)
P1_TCK: J101.17 (TCK_1V8), R730.1, U721.11 (NO1)
P1_TDI: J101.15 (TDI_1V8), U721.13 (NO2)
P1_TDO: J101.18 (TDO_1V8), U721.17 (NO4)
P1_TMS: J101.2 (TMS_1V8), U721.15 (NO3)
P2_TARGET_SENSE: J102.1 (TARGET_SENSE_1V8), U722.18 (NO5)
P2_TCK: J102.17 (TCK_1V8), R731.1, U722.11 (NO1)
P2_TDI: J102.15 (TDI_1V8), U722.13 (NO2)
P2_TDO: J102.18 (TDO_1V8), U722.17 (NO4)
P2_TMS: J102.2 (TMS_1V8), U722.15 (NO3)
P3_TARGET_SENSE: J103.1 (TARGET_SENSE_1V8), U723.18 (NO5)
P3_TCK: J103.17 (TCK_1V8), R732.1, U723.11 (NO1)
P3_TDI: J103.15 (TDI_1V8), U723.13 (NO2)
P3_TDO: J103.18 (TDO_1V8), U723.17 (NO4)
P3_TMS: J103.2 (TMS_1V8), U723.15 (NO3)
P4_TARGET_SENSE: J104.1 (TARGET_SENSE_1V8), U724.18 (NO5)
P4_TCK: J104.17 (TCK_1V8), R733.1, U724.11 (NO1)
P4_TDI: J104.15 (TDI_1V8), U724.13 (NO2)
P4_TDO: J104.18 (TDO_1V8), U724.17 (NO4)
P4_TMS: J104.2 (TMS_1V8), U724.15 (NO3)
P5_TARGET_SENSE: J105.1 (TARGET_SENSE_1V8), U725.18 (NO5)
P5_TCK: J105.17 (TCK_1V8), R734.1, U725.11 (NO1)
P5_TDI: J105.15 (TDI_1V8), U725.13 (NO2)
P5_TDO: J105.18 (TDO_1V8), U725.17 (NO4)
P5_TMS: J105.2 (TMS_1V8), U725.15 (NO3)
P6_TARGET_SENSE: J106.1 (TARGET_SENSE_1V8), U726.18 (NO5)
P6_TCK: J106.17 (TCK_1V8), R735.1, U726.11 (NO1)
P6_TDI: J106.15 (TDI_1V8), U726.13 (NO2)
P6_TDO: J106.18 (TDO_1V8), U726.17 (NO4)
P6_TMS: J106.2 (TMS_1V8), U726.15 (NO3)
P7_TARGET_SENSE: J107.1 (TARGET_SENSE_1V8), U727.18 (NO5)
P7_TCK: J107.17 (TCK_1V8), R736.1, U727.11 (NO1)
P7_TDI: J107.15 (TDI_1V8), U727.13 (NO2)
P7_TDO: J107.18 (TDO_1V8), U727.17 (NO4)
P7_TMS: J107.2 (TMS_1V8), U727.15 (NO3)
P8_TARGET_SENSE: J108.1 (TARGET_SENSE_1V8), U728.18 (NO5)
P8_TCK: J108.17 (TCK_1V8), R737.1, U728.11 (NO1)
P8_TDI: J108.15 (TDI_1V8), U728.13 (NO2)
P8_TDO: J108.18 (TDO_1V8), U728.17 (NO4)
P8_TMS: J108.2 (TMS_1V8), U728.15 (NO3)
PCIE_AUX_FAULT_N: R18.1, TP21.1 (PIN_1), U5.4 (F\A\U\L\T\)
PCIE_AUX_ILIM: R24.2, U5.5 (ILIM)
PCIE_PERST_B_3V3: J6.A11 (PERST#), R21.1, R22.2, TP14.1 (PIN_1), U4.4 (B)
PCIE_PERST_B_VIO: R7.1, R8.1, R12.2, R20.1, TP13.1 (PIN_1), U4.3 (A)
PCIE_PERST_VCCA: C11.2, R1.1, R2.1, R20.2, U4.1 (Vcca)
PCIE_PRSNT1_B: J6.A1 (PRSNT1#), R27.2, R28.2, R29.2
PCIE_REFCLKN_C: C8.1, J6.A14 (REFCLK-)
PCIE_REFCLKP_C: C7.1, J6.A13 (REFCLK+)
PCIE_RX0N_C: C14.1, J6.A17 (PERn0)
PCIE_RX0P_C: C13.1, J6.A16 (PERp0)
PCIE_RX1N_C: C16.1, J6.A22 (PERn1)
PCIE_RX1P_C: C15.1, J6.A21 (PERp1)
PCIE_RX2N_C: C18.1, J6.A26 (PERn2)
PCIE_RX2P_C: C17.1, J6.A25 (PERp2)
PCIE_RX3N_C: C20.1, J6.A30 (PERn3)
PCIE_RX3P_C: C19.1, J6.A29 (PERp3)
PCIE_SMBUS_VREF2: C10.2, R13.1, U2.7 (VREF2), U2.8 (EN)
PCIE_SMCLK_3V3: J6.B5 (SMCLK), R17.1, TP11.1 (PIN_1), U2.5 (SDA2)
PCIE_SMCLK_VIO: R11.1, R14.1, TP12.1 (PIN_1), U2.4 (SDA1)
PCIE_SMDAT_3V3: J6.B6 (SMDAT), R16.1, TP10.1 (PIN_1), U2.6 (SCL2)
PCIE_SMDAT_VIO: R10.1, R15.1, TP9.1 (PIN_1), U2.3 (SCL1)
PCIE_VIO_INVERTED: Q1.5 (G2), Q1.6 (D1), R30.1
PCIE_WAKE_B_3V3: J6.B11 (WAKE#), R26.1, TP16.1 (PIN_1), U6.6 (SCL2)
PCIE_WAKE_B_VIO: R9.1, R25.1, TP15.1 (PIN_1), U6.3 (SCL1)
PCIE_WAKE_VREF2: C28.2, R23.1, U6.7 (VREF2), U6.8 (EN)
SEL_0: R611.1, SW600.1 (POS1), U620.3 (~MR)
SEL_1: R621.2, SW600.2 (POS2), U710.2 (A1)
SEL_2: R631.2, SW600.3 (POS3), U710.3 (A2)
SEL_3: R641.2, SW600.4 (POS4), U710.4 (A3)
SEL_4: R651.2, SW600.5 (POS5), U710.5 (A4)
SEL_5: R661.2, SW600.6 (POS6), U710.6 (A5)
SEL_6: R671.2, SW600.7 (POS7), U710.7 (A6)
SEL_7: R681.2, SW600.8 (POS8), U710.8 (A7)
SEL_8: R691.2, SW600.9 (POS9), U710.9 (A8)
USB5V: C506.2, C520.1, D500.5 (VBUS), FB502.1, J500.A4 (VBUS), J500.A9 (VBUS), J500.B4 (VBUS), J500.B9 (VBUS), U506.1 (IN), U506.3 (EN)
USB_DM_CONN: D500.3 (I/O2), J500.A7 (DN1), J500.B7 (DN2)
USB_DP_CONN: D500.1 (I/O1), J500.A6 (DP1), J500.B6 (DP2)
USB_D_N: D500.4 (I/O2), U501.6 (DM)
USB_D_P: D500.6 (I/O1), U501.7 (DP)
USB_SELECT_ENABLE_3V3: R600.1, R700.1, SW600.A (COMMON), SW700.2 (USB_ENABLE_COMMON), U621.3 (~MR)
VIO1: C9.2, C27.2, MC1.1 (VIO1), Q1.2 (G1), R1.2, R14.2, R15.2, R25.2, R33.2, U2.2 (VREF1), U6.2 (VREF1)
VIO_PG: Q1.3 (D2), R31.1, R32.2, U5.3 (EN)
VREFP: MC2.79 (VREFP), R6.2
XEM_USB_OE: R613.1, U610.8 (OE), U630.4 (Y)
XEM_USB_TCK: R614.2, U700.2 (S1A)
XEM_USB_TDI: R615.2, U700.11 (S3A)
XEM_USB_TDO: U610.10 (B4_TDO), U700.14 (S4A)
XEM_USB_TMS: R616.2, U700.5 (S2A)

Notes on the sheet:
XEM8310 CARRIER / V10 / V9 SHARED POWER + JTAG / ROUGH PCB PLACEMENT
EIGHT GT RECORDING PORTS | REGULAR-I/O STIMULATION | PCIe x4 TO PC | ONE SHARED HDMI SUPPLY | NINE JTAG TARGETS
V9 circuit paired with V10 six-layer rough placement: eight GT recording ports, regular-I/O stimulation and PCIe x4. Shared power/JTAG components placed; new routing, refill and hardware validation remain pending.
09 PCIe x4 / GTY225 / x8 EDGE
Function: Connect four PCIe lanes to the PC using GTY225. Only physical lanes0-3 are wired; lanes4-7 are NC. Source / changes: Opal Kelly BRK8310-A01 sheet2 (PCIe), https://pins.opalkelly.com/downloads/442/download?category_id=3 . V7 removes C21-C26/C29/C30 and all upper-lane signal links. Retains 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
14 PCIe CONTROL / RESET / POWER-DOMAIN SUPPORT
SMBus TRANSLATION
Function: Translates the PCIe SMBus clock/data lines between the host auxiliary 3.3 V domain and module VIO1. Source / changes: Opal Kelly BRK8310 A01 schematic, sheet 2, U2 SMBus circuit. https://pins.opalkelly.com/downloads/442/download?category_id=3 . Original refs/values/connections retained; R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
RESET TRANSLATION
Function: Translates the active-low host PCIe reset into the selected 1.2 V FPGA reset domain. Source / changes: Opal Kelly BRK8310 A01 schematic, sheet 2, U4 PERST circuit. https://pins.opalkelly.com/downloads/442/download?category_id=3 . Original refs/values/pins retained; R12/R20/R21/R22 DNP. Ne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
WAKE TRANSLATION
Function: Translates active-low FPGA WAKE to the PCIe host auxiliary-power domain. Source / changes: Opal Kelly BRK8310 A01 schematic, sheet 2, U6 WAKE circuit. https://pins.opalkelly.com/downloads/442/download?category_id=3 . Original refs/values/pins retained; R26 DNP. NetC28_2 is named PCIE_WAKE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
AUXILIARY ISOLATION
Function: Enables the PCIe auxiliary-powered translator circuitry only when the module VIO power-good condition is present. Source / changes: Opal Kelly BRK8310 A01 schematic, sheet 2, U5 auxiliary load switch. https://pins.opalkelly.com/downloads/442/download?category_id=3 . Original refs/values/p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
VIO POWER GOOD
Function: Generates the VIO-present condition used to isolate PCIe level translators during module power loss. Source / changes: Opal Kelly BRK8310 A01 schematic, sheet 2, Q1 VIO power-good circuit. https://pins.opalkelly.com/downloads/442/download?category_id=3 . Both original Q1 units and R30-R33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
MODULE PIN SELECTORS
Function: Selects fixed-1.2-V PERST and connects the remaining PCIe sidebands to their original module pins. Source / changes: Opal Kelly BRK8310 A01 schematic, sheet 1, R1/R2/R7-R11 selectors. https://pins.opalkelly.com/downloads/442/download?category_id=3 . References and 0-ohm values retained. D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
10 MC1 / XEM8310 MODULE MATING
Function: Mate to the XEM8310; Bank64 L1-L8 drive eight ordinary LVDS stimulation-command pairs. The module supplies VIO1 and1.8V; the unused old HP recording inputs are explicitly NC. Source / changes: Opal Kelly BRK8310-A01 sheet1 and official Pins: https://pins.opalkelly.com/pin_list/XEM8310 . C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
11 MC2 / XEM8310 MODULE MATING
Function: Selects the module internal SYSMON reference. Source / changes: BRK8310-A01 sheet1: R6=0R fitted by Default variant; external U1/C1-C3/R5 DNP option omitted. Connections VREFP to GNDADC unchanged. https://docs.opalkelly.com/xem8310/expansion-connectors/
Function: Mates the custom carrier to the purchased XEM8310. All80 contact numbers are retained; matching globals carry assigned signals. NC marks denote deliberately unused contacts in this revision. Source / changes: Opal Kelly BRK8310-A01 sheet1 and official XEM8310 Pins (25 Oct 2026): https://p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
12 MC3 / XEM8310 MODULE MATING
Function: Mate all12 GTY channels, PCIe reference clock and fixed1.2V sideband supply to XEM8310. GTY224/226 RX0-3 serve eight recording ports; GTY225 RX/TX0-3 serve PCIe physical lanes3-0. Source / changes: Opal Kelly BRK8310-A01 sheet1; https://pins.opalkelly.com/pin_list/XEM8310 . Codex V7 repur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
13 MAIN INPUT / LOCAL XEM JTAG / INDICATORS
MODULE INPUT: 7.5–15 V
Function: Supply XEM8310 +VDCIN from one selected input. J4 and J5 are alternatives: connect only one source.
Source / changes: Opal Kelly BRK8310-A01, sheet 1, J4/J5/C5/C6. Original refs, values and pin/net connections retained; redrawn. https://pins.opalkelly.com/downloads/442/download?category_id=3 V6 adds source/return ERC flags at the actual external entry. Only ONE input source: no J4/J5 ORing circui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
MODULE 1.8 V JTAG
Function: Connect an external 1.8 V programmer to XEM8310 JTAG. C4 bypasses the local module 1.8 V reference.
Source / changes: Opal Kelly BRK8310-A01, sheet 1, J3/C4. Original refs, values, JTAG pin numbers and net connections retained. https://pins.opalkelly.com/downloads/442/download?category_id=3 Redrawn symbol geometry. Level translation and hardware target selection are implemented in the V5 blocks b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
MODULE / INPUT POWER INDICATORS
+3.3 V MODULE
+VDCIN
Function: Indicate module +3.3 V and main-input presence using two inherited resistor / LED branches.
Source / changes: Opal Kelly BRK8310-A01, sheet 1, R3/D1 and R4/D2. R3=549 Ω, R4=2.00 kΩ; original pin connections retained. https://pins.opalkelly.com/downloads/442/download?category_id=3 Visible values simplified; green LED PN unchanged. R4 input-voltage / thermal derating remains open.
HDMI POWER / ONE SHARED SUPPLY BELOW
Function: J500 is the USB2 device input. CC1/CC2 use 5.1k pulldowns; shield uses 100nF and a 220ohm@100MHz ferrite to GND. USB5V feeds the FTDI core through the source filter. Source / changes: Codex extraction from the BRK8305 A03-derived Carrier_V1 J4 USB-C adaptation. Original BRK J500/R500/R501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
Function: U501 is a USB2-to-JTAG MPSSE host. HOST_TCK/TDI/TMS are3.3V outputs; HOST_TDO is an input. U505 holds cable configuration; Y500 is12MHz. FTDI3V3 is an internal regulator rail. Source / changes: BRK8305 A03,25Oct2023,JTAG sheet8/PDFp4: https://pins.opalkelly.com/downloads/583/download?cate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

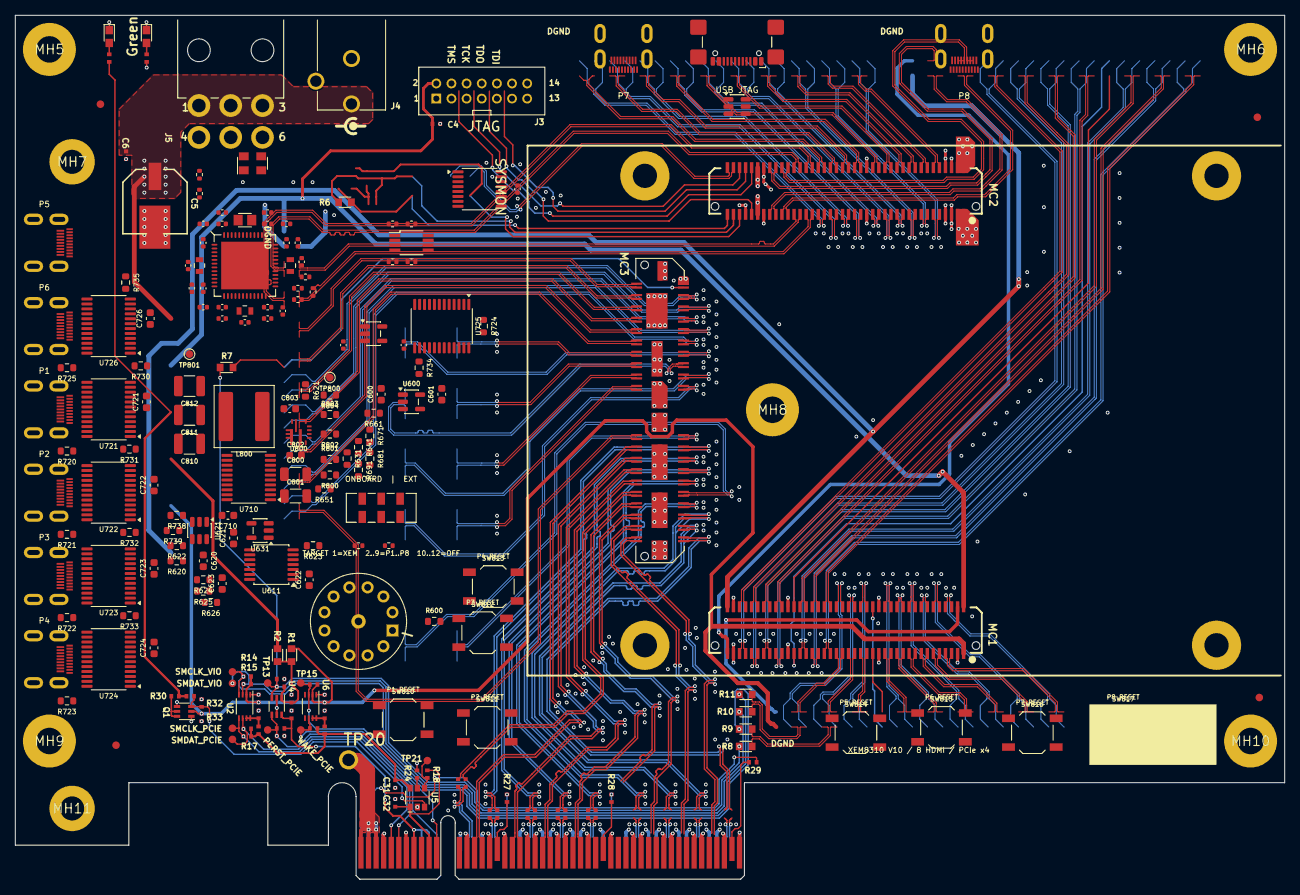
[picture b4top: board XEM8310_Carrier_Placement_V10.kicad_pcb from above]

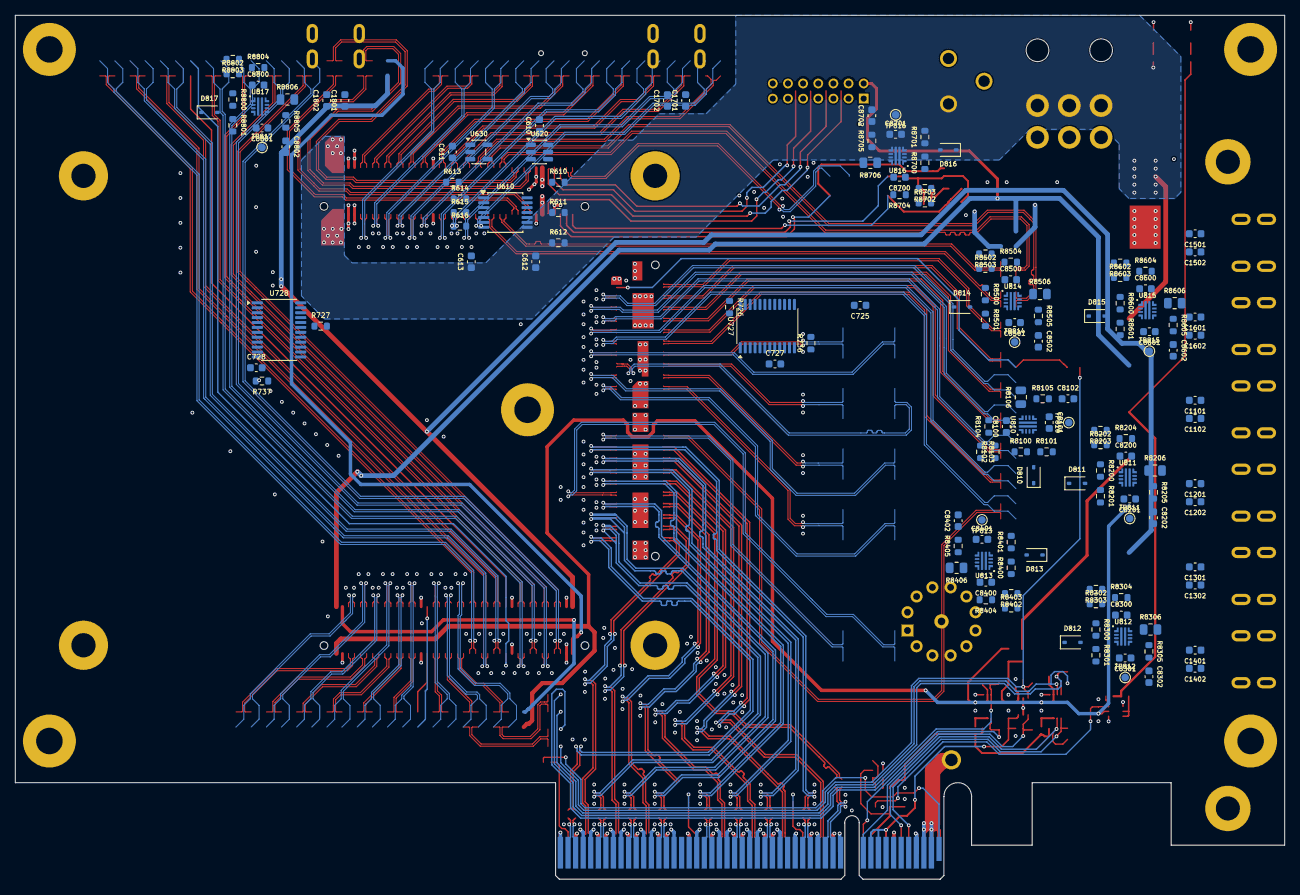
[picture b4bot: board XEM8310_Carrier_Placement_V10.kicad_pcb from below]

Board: 6 copper layers, 167.6 x 114.1 mm, 366 parts (143 on the bottom side), 293 nets.

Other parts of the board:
FID1: FIDUCIAL; FID1
FID2: FIDUCIAL; FID2
FID3: FIDUCIAL; FID3
FID4: FIDUCIAL; FID4
MH1: MTG; MH1
MH2: MTG; MH2
MH3: MTG; MH3
MH4: MTG; MH4
MH5: MH5
MH6: MH6
MH7: MH7
MH8: MH8
MH9: MH9
MH10: MH10
MH11: MH11

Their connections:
DGND: MH6.MH; also elsewhere on the board
